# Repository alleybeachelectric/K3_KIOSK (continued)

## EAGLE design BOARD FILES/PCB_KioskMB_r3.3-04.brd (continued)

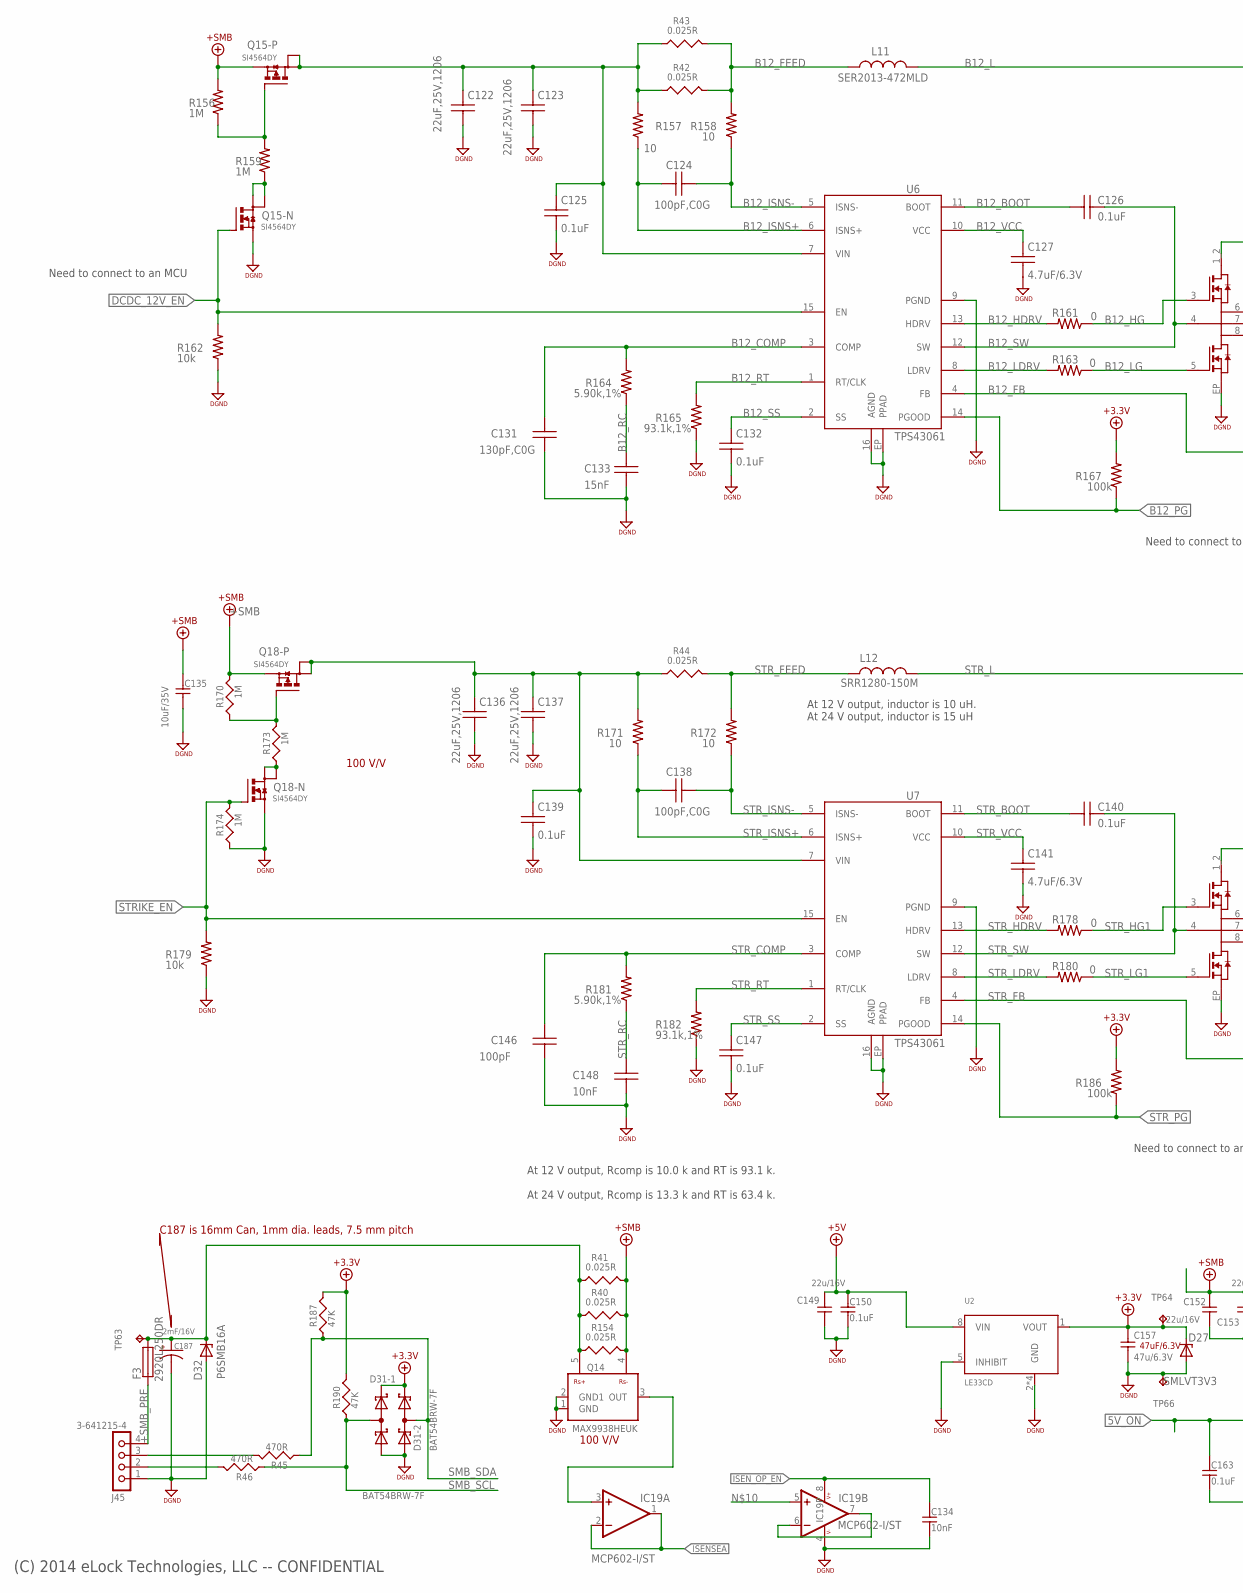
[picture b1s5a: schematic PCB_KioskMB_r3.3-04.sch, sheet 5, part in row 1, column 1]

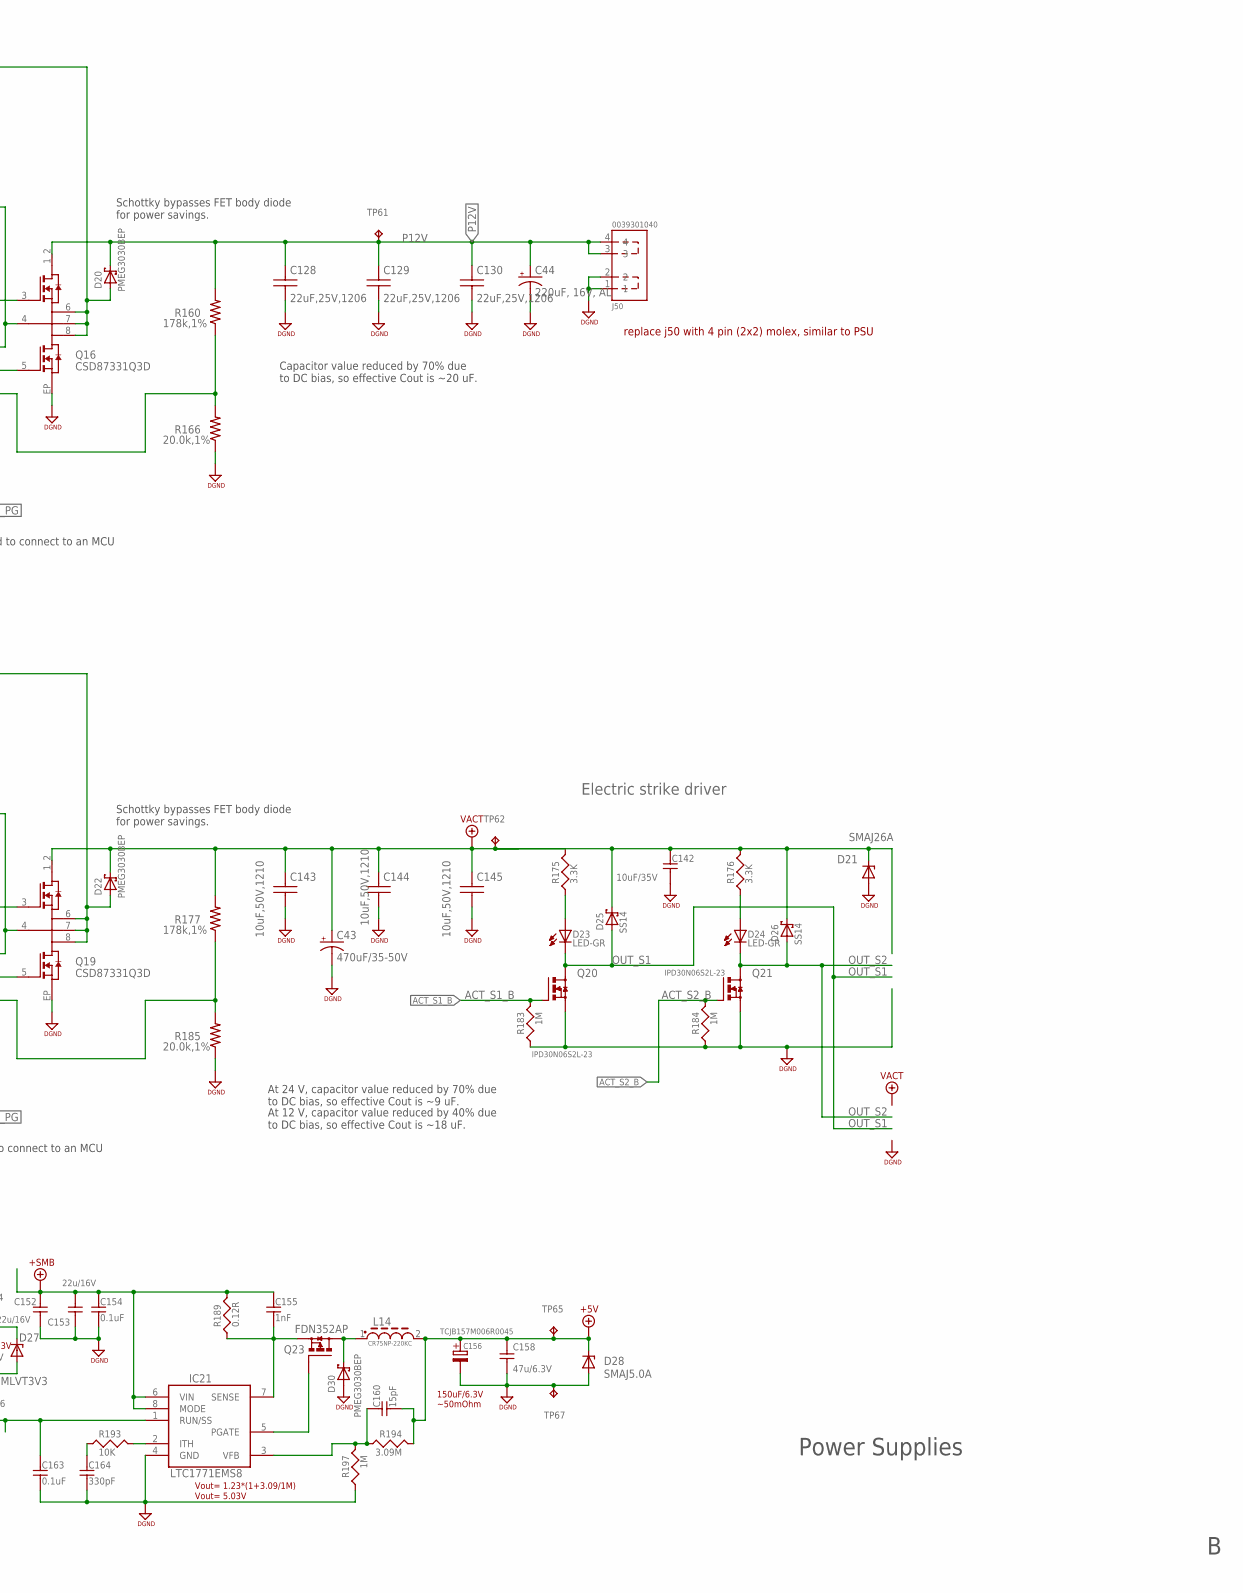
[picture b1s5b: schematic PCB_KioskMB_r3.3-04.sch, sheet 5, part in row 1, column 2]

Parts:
C43: 470uF/35-50V; E5-13
C44: 220uF, 16V, AL; 153CLV-0605
C122, C123, C128, C129, C130, C136, C137: 22uF,25V,1206; C1206; MFR_PN CL31A226KAHNNNE
C124, C138: 100pF,C0G; C0603; MFR_PN CL10C101JB8NCNC
C125, C126, C132, C139, C140, C147: 0.1uF; C0603; MFR_PN GRM188R71H104KA93D
C127, C141: 4.7uF/6.3V; C0603; MFR_PN CL10A475KA8NQNC
C131: 130pF,C0G; C0603; MFR_PN CL10C131JB8NNNC
C133: 15nF; C0603; MFR_PN CL10B153KB8NNNC
C134: 10nF; 0603
C135, C142: 10uF/35V; 1206
C143, C144, C145: 10uF,50V,1210; C1210; MFR_PN CL32B106KBJNNWE
C146: 100pF; C0603; MFR_PN CL10C101JB8NNNC
C148: 10nF; C0603; MFR_PN CL10B103KB8NNNC
C149, C152, C153: 22u/16V; 1210
C150, C154, C163: 0.1uF; 0603
C155: 1nF; 0603
C156: TCJB157M006R0045; 3528-POL
C157, C158: 47u/6.3V; 1210
C160: 15pF; 0603
C164: 330pF; 0603
C187: 2mF/16V; E7,5-18
D20, D22, D30: PMEG3030BEP; SOD-128
D21: SMAJ26A; SMA
D23, D24: LED-GR; 0805-POL
D25, D26: SS14; SMA
D27: SMLVT3V3; SMA
D28: SMAJ5.0A; SMA
D31: BAT54BRW-7F; SOT-363
D32: P6SMB16A; SMB
F3: 2920L250DR; 1812
IC19: MCP602-I/ST; TSSOP8
IC21: LTC1771EMS8; MSOP-08
J45: 3-641215-4
J50: 0039301040
L11: SER2013-472MLD; L_SER20XX; MFR_PN SER2013-472ML
L12: SRR1280-150M; L_SRR1280; MFR_PN SRR1280-1x0M
L14: CR75NP-220KC; CR75
Q14: MAX9938HEUK; SOT23-5
Q15, Q18: SI4564DY; SO-08
Q16, Q19: CSD87331Q3D; SON8_3.3X3.3_TI; MFR_PN CSD87331Q3D
Q20, Q21: IPD30N06S2L-23; TO252
Q23: FDN352AP; SOT-23
R40, R41, R42, R43, R44, R154: 0.025R; 0805
R45, R46: 470R; 0603
R156, R159: 1M; R0603; MFR_PN ERJ-3GEYJ104V
R157, R158, R171, R172: 10; R0603; MFR_PN MCR03ERTJ100
R160, R177: 178k,1%; R0603; MFR_PN ERJ-3EKF1783V
R161, R163, R178, R180: 0; R0603; MFR_PN ERJ-3GEY0R00V
R162, R179: 10k; R0603; MFR_PN ERJ-3GEYJ103V
R164: 5.90k,1%; R0603; MFR_PN ERJ-3EKF5901V
R165: 93.1k,1%; R0603; MFR_PN ERJ-3EKF9312V
R166, R185: 20.0k,1%; R0603; MFR_PN ERJ-3EKF2002V
R167, R186: 100k; R0603; MFR_PN ERJ-3GEYJ104V
R170, R173, R174, R183, R184, R197: 1M; 0603
R175, R176: 3.3K; 0805
R181: 5.90k,1%; R0603; MFR_PN ERJ-3EKFxxxxV
R182: 93.1k,1%; R0603; MFR_PN ERJ-3EKFxxxxV
R187, R190: 47K; 0603
R189: 0.12R; 0805
R193: 10K; 0603
R194: 3.09M; 0603
TP61, TP62, TP63, TP64, TP65, TP66, TP67: TPB1,27; B1,27
U2: LE33CD; LE33
U6, U7: TPS43061; QFN16_3X3_EP

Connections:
5V_ON: C163.1, IC21.1 (RUN/SS); also elsewhere on the board
+3.3V: C157.1, D27.+ (C), D31.4 (K), D31.5 (K), R167.2, R186.2, R187.2, R190.2, TP64.TP, U2.1 (VOUT); also elsewhere on the board
+5V: C149.1, C150.1, C156.1 (PIN+), C158.1, C160.2, D28.+ (C), L14.2, R194.1, TP65.TP, U2.8 (VIN); also elsewhere on the board
+SMB: C135.1, C152.1, C153.1, C154.1, C155.1, IC21.6 (VIN), IC21.8 (MODE), Q14.4 (VIN-), Q15.3 (S), Q18.3 (S), R40.2, R41.2, R154.2, R156.2, R170.1, R189.2; also elsewhere on the board
+SMB_PRE: F3.1, J45.4; also elsewhere on the board
ACT_S1_B: Q20.1 (G), R183.1; also elsewhere on the board
ACT_S2_B: Q21.1 (G), R184.1; also elsewhere on the board
B12_BOOT: C126.1, U6.11 (BOOT)
B12_COMP: C131.1, R164.2, U6.3 (COMP)
B12_FB: R160.1, R166.2, U6.4 (FB)
B12_FEED: L11.2, R42.2, R43.2, R158.2
B12_HDRV: R161.2, U6.13 (HDRV)
B12_HG: Q16.3 (TG), R161.1
B12_ISNS+: C124.1, R157.1, U6.6 (ISNS+)
B12_ISNS-: C124.2, R158.1, U6.5 (ISNS-)
B12_L: D20.A, L11.1, Q16.6 (VSW), Q16.7 (VSW), Q16.8 (VSW)
B12_LDRV: R163.2, U6.8 (LDRV)
B12_LG: Q16.5 (BG), R163.1
B12_PG: R167.1, U6.14 (PGOOD); also elsewhere on the board
B12_RC: C133.1, R164.1
B12_RT: R165.2, U6.1 (RT/CLK)
B12_SS: C132.1, U6.2 (SS)
B12_SW: C126.2, Q16.4 (TGR), U6.12 (SW)
B12_VCC: C127.1, U6.10 (VCC)
DCDC12VIN: C122.1, C123.1, C125.1, Q15.5 (D), Q15.6 (D1), R42.1, R43.1, R157.2, U6.7 (VIN)
DCDC_12V_EN: Q15.2 (G), R162.2, U6.15 (EN); also elsewhere on the board
DGND: C43.-, C44.-, C122.2, C123.2, C125.2, C127.2, C128.2, C129.2, C130.2, C131.2, C132.2, C133.2, C134.2, C135.2, C136.2, C137.2, C139.2, C141.2, C142.2, C143.2, C144.2, C145.2, C146.2, C147.2, C148.2, C149.2, C150.2, C152.2, C153.2, C154.2, C156.2 (PIN-), C157.2, C158.2, C163.2, C164.2, C187.-, D21.- (A), D27.- (A), D28.- (A), D30.A, D31.1 (A), D31.2 (A), D32.A, IC19.4 (V-), IC21.4 (GND), J45.1, J50.1, J50.2, Q14.1 (GND), Q14.2 (GND1), Q15.1 (S), Q16.EP (PGND), Q18.1 (S), Q19.EP (PGND), Q20.2 (S), Q21.2 (S), R162.1, R165.1, R166.1, R174.2, R179.1, R182.1, R183.2, R184.2, R185.1, R197.2, TP66.TP, TP67.TP, U2.2 (GND), U2.3 (GND), U2.5 (INHIBIT), U2.6 (GND), U2.7 (GND), U6.9 (PGND), U6.16 (AGND), U6.EP (PPAD), U7.9 (PGND), U7.16 (AGND), U7.EP (PPAD); also elsewhere on the board
ISENSEA: IC19.1 (OUT), IC19.2 (-IN); also elsewhere on the board
ISEN_OP_EN: C134.1, IC19.8 (V+); also elsewhere on the board
unnamed: IC19.6 (-IN), IC19.7 (OUT)
unnamed: IC21.5 (PGATE), Q23.1 (G)
unnamed: C187.+, D32.C, F3.2, Q14.5 (VIN+), R40.1, R41.1, R154.1, TP63.TP
unnamed: IC19.3 (+IN), IC19.5 (+IN), Q14.3 (OUT)
unnamed: IC21.2 (ITH), R193.2
unnamed: C164.1, R193.1
unnamed: D30.K, L14.1, Q23.3 (D)
unnamed: C155.2, IC21.7 (SENSE), Q23.2 (S), R189.1
unnamed: Q15.4 (G), R156.1, R159.2
unnamed: C160.1, IC21.3 (VFB), R194.2, R197.1
unnamed: J45.2, R46.2
unnamed: D23.2 (A), R175.1
unnamed: D24.2 (A), R176.1
unnamed: J45.3, R45.2
unnamed: Q18.4 (G), R170.2, R173.1
unnamed: Q15.7 (D), Q15.8 (D1), R159.1
unnamed: Q18.7 (D), Q18.8 (D1), R173.2
OUT_S1: D23.1+ (K), D25.A, Q20.3 (D); also elsewhere on the board
OUT_S2: D24.1+ (K), D26.A, Q21.3 (D); also elsewhere on the board
P12V: C44.+, C128.1, C129.1, C130.1, D20.K, J50.3, J50.4, Q16.1_2 (VIN), R160.2, TP61.TP; also elsewhere on the board
SMB_SCL: D31.6 (AK), R46.1, R190.1; also elsewhere on the board
SMB_SDA: D31.3 (AK), R45.1, R187.1; also elsewhere on the board
STRIKE_EN: Q18.2 (G), R174.1, R179.2, U7.15 (EN); also elsewhere on the board
STR_BOOT: C140.1, U7.11 (BOOT)
STR_COMP: C146.1, R181.2, U7.3 (COMP)
STR_FB: R177.1, R185.2, U7.4 (FB)
STR_FEED: L12.2, R44.2, R172.2
STR_HDRV: R178.2, U7.13 (HDRV)
STR_HG1: Q19.3 (TG), R178.1
STR_ISNS+: C138.1, R171.1, U7.6 (ISNS+)
STR_ISNS-: C138.2, R172.1, U7.5 (ISNS-)
STR_L: D22.A, L12.1, Q19.6 (VSW), Q19.7 (VSW), Q19.8 (VSW)
STR_LDRV: R180.2, U7.8 (LDRV)
STR_LG1: Q19.5 (BG), R180.1
STR_PG: R186.1, U7.14 (PGOOD); also elsewhere on the board
STR_RC: C148.1, R181.1
STR_RT: R182.2, U7.1 (RT/CLK)
STR_SS: C147.1, U7.2 (SS)
STR_SW: C140.2, Q19.4 (TGR), U7.12 (SW)
STR_VCC: C141.1, U7.10 (VCC)
VACT: C43.+, C142.1, C143.1, C144.1, C145.1, D21.+ (C), D22.K, D25.C (K), D26.C (K), Q19.1_2 (VIN), R175.2, R176.2, R177.2, TP62.TP; also elsewhere on the board
VSUPLYACT: C136.1, C137.1, C139.1, Q18.5 (D), Q18.6 (D1), R44.1, R171.2, U7.7 (VIN)

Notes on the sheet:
(C) 2014 eLock Technologies, LLC -- CONFIDENTIAL
Power Supplies
Schottky bypasses FET body diode for power savings.
Capacitor value reduced by 70% due to DC bias, so effective Cout is ~20 uF.
At 24 V, capacitor value reduced by 70% due to DC bias, so effective Cout is ~9 uF.
At 12 V, capacitor value reduced by 40% due to DC bias, so effective Cout is ~18 uF.
At 12 V output, inductor is 10 uH. At 24 V output, inductor is 15 uH
At 12 V output, Rcomp is 10.0 k and RT is 93.1 k. At 24 V output, Rcomp is 13.3 k and RT is 63.4 k.
47uF/6.3V
Electric strike driver
100 V/V
Vout= 1.23*(1+3.09/1M)
Vout= 5.03V
150uF/6.3V ~50mOhm
Need to connect to an MCU
C187 is 16mm Can, 1mm dia. leads, 7.5 mm pitch
replace j50 with 4 pin (2x2) molex, similar to PSU

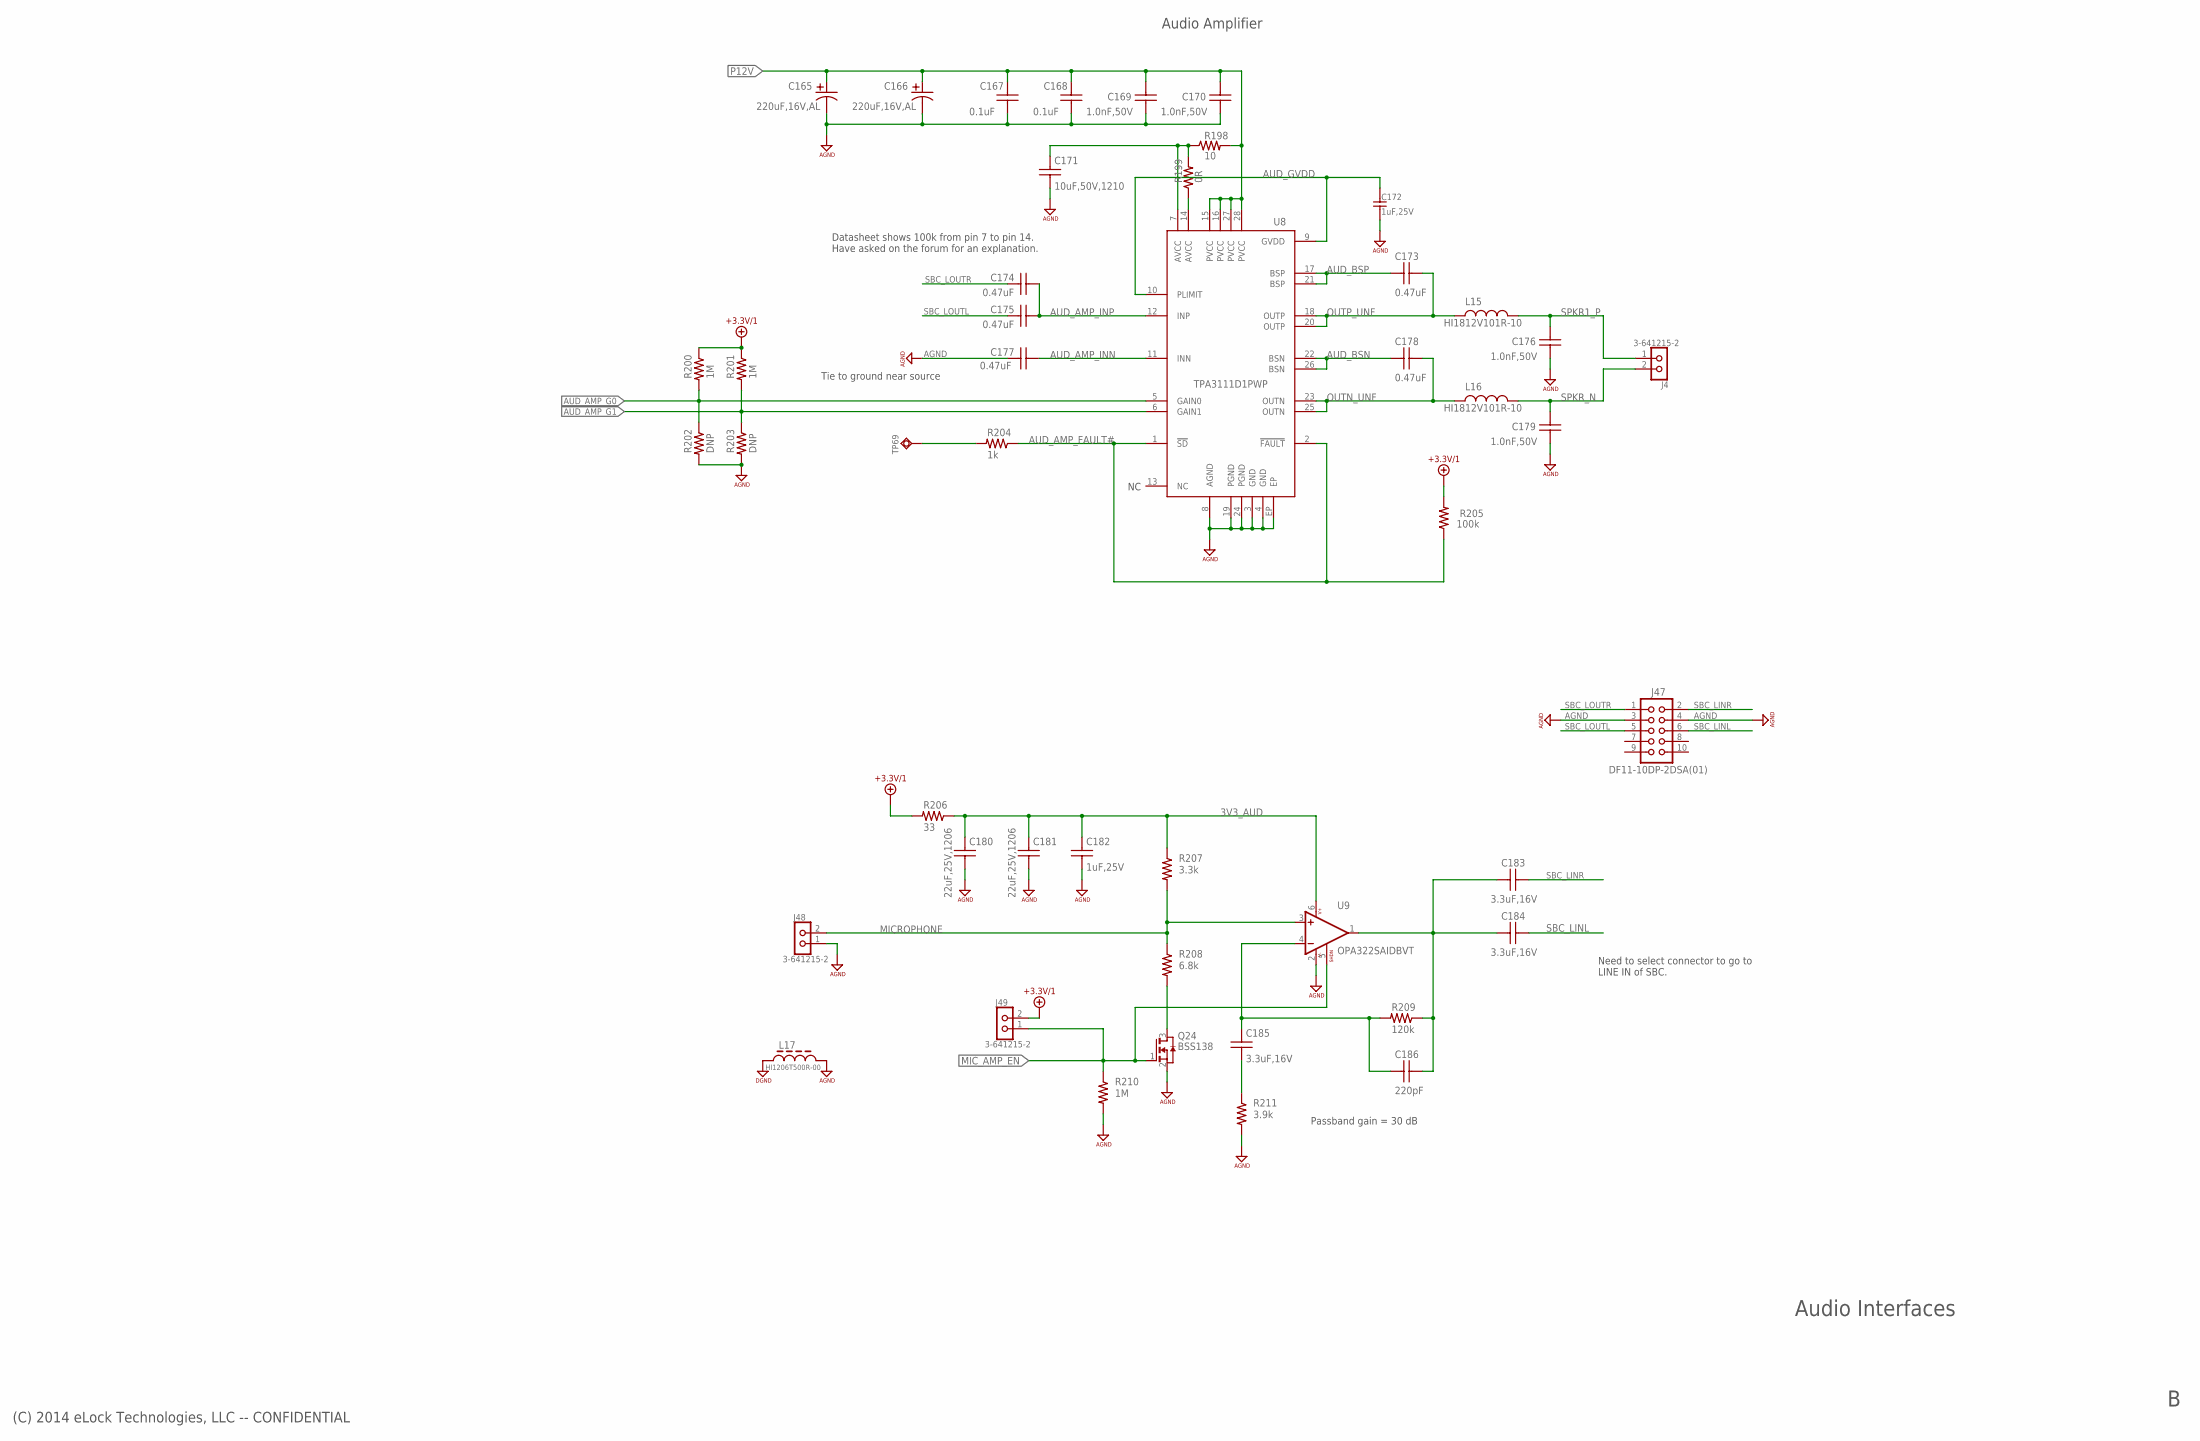
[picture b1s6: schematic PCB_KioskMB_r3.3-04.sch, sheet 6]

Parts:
C165, C166: 220uF,16V,AL; CAP_6.3MM_DIA_SMT; MFR_PN EEV227M016A9HAA
C167, C168: 0.1uF; C0603
C169, C170, C176, C179: 1.0nF,50V; C0603; MFR_PN CL10B102KB8NNNC
C171: 10uF,50V,1210; C1210; MFR_PN CL32B106KBJNNWE
C172: 1uF,25V; 0603
C173, C178: 0.47uF; C0603; MFR_PN TMK107B7474KA-TR
C174, C175, C177: 0.47uF; C0603; MFR_PN CL10B153KB8NNNC
C180, C181: 22uF,25V,1206; C1206; MFR_PN CL31A226KAHNNNE
C182: 1uF,25V; C0603
C183, C184, C185: 3.3uF,16V; C0603
C186: 220pF; C0603
J4, J48, J49: 3-641215-2
J47: DF11-10DP-2DSA(01); DF11-10DP-2DSA
L15, L16: HI1812V101R-10; L1812; MFR_PN HI1812V101R-10
L17: HI1206T500R-00; 1206
Q24: BSS138; SOT23
R198: 10; R0603; MFR_PN MCR03ERTJ100
R199: 0R; R0603; MFR_PN MCR03ERTJ100
R200, R201, R210: 1M; R0603
R202, R203: DNP; R0603
R204: 1k; R0603
R205: 100k; R0603
R206: 33; R0603
R207: 3.3k; R0603
R208: 6.8k; R0603
R209: 120k; R0603
R211: 3.9k; R0603
TP69: P1-13; P1-13@1
U8: TPA3111D1PWP; TSSOP28_EP
U9: OPA322SAIDBVT; SOT23-6

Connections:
3V3_AUD: C180.1, C181.1, C182.1, R206.1, R207.1, U9.6 (V+)
+3.3V/1: J49.2, R200.1, R201.1, R205.2, R206.2; also elsewhere on the board
AGND: C165.2, C166.2, C167.2, C168.2, C169.2, C170.2, C171.2, C172.2, C176.2, C177.1, C179.2, C180.2, C181.2, C182.2, J47.3, J47.4, J48.1, L17.2, Q24.2 (S), R202.2, R203.2, R210.2, R211.2, U8.3 (GND), U8.4 (GND), U8.8 (AGND), U8.19 (PGND), U8.24 (PGND), U8.EP, U9.2 (V-); also elsewhere on the board
AUD_AMP_FAULT#: R204.1, R205.1, U8.1 (!SD), U8.2 (!FAULT)
AUD_AMP_G0: R200.2, R202.1, U8.5 (GAIN0); also elsewhere on the board
AUD_AMP_G1: R201.2, R203.1, U8.6 (GAIN1); also elsewhere on the board
AUD_AMP_INN: C177.2, U8.11 (INN)
AUD_AMP_INP: C174.2, C175.2, U8.12 (INP)
AUD_AMP_SD#: R204.2, TP69.1
AUD_BSN: C178.1, U8.22 (BSN), U8.26 (BSN)
AUD_BSP: C173.1, U8.17 (BSP), U8.21 (BSP)
AUD_GVDD: C172.1, U8.9 (GVDD), U8.10 (PLIMIT)
DGND: L17.1; also elsewhere on the board
MICROPHONE: J48.2, R207.2, R208.1, U9.3 (+IN); also elsewhere on the board
MIC_AMP_EN: J49.1, Q24.1 (G), R210.1, U9.5 (!SHDN); also elsewhere on the board
unnamed: R199.1, U8.14 (AVCC)
unnamed: C171.1, R198.1, R199.2, U8.7 (AVCC)
unnamed: C185.2, R211.1
unnamed: C185.1, C186.1, R209.2, U9.4 (-IN)
unnamed: C183.1, C184.1, C186.2, R209.1, U9.1 (OUT)
unnamed: Q24.3 (D), R208.2
OUTN_UNF: C178.2, L16.2, U8.23 (OUTN), U8.25 (OUTN)
OUTP_UNF: C173.2, L15.2, U8.18 (OUTP), U8.20 (OUTP)
P12V: C165.1, C166.1, C167.1, C168.1, C169.1, C170.1, R198.2, U8.15 (PVCC), U8.16 (PVCC), U8.27 (PVCC), U8.28 (PVCC); also elsewhere on the board
SBC_LINL: C184.2, J47.6; also elsewhere on the board
SBC_LINR: C183.2, J47.2; also elsewhere on the board
SBC_LOUTL: C175.1, J47.5; also elsewhere on the board
SBC_LOUTR: C174.1, J47.1; also elsewhere on the board
SPKR1_P: C176.1, J4.1, L15.1; also elsewhere on the board
SPKR_N: C179.1, J4.2, L16.1; also elsewhere on the board

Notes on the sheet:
(C) 2014 eLock Technologies, LLC -- CONFIDENTIAL
Audio Interfaces
Tie to ground near source
Datasheet shows 100k from pin 7 to pin 14. Have asked on the forum for an explanation.
Audio Amplifier
Passband gain = 30 dB
Need to select connector to go to LINE IN of SBC.

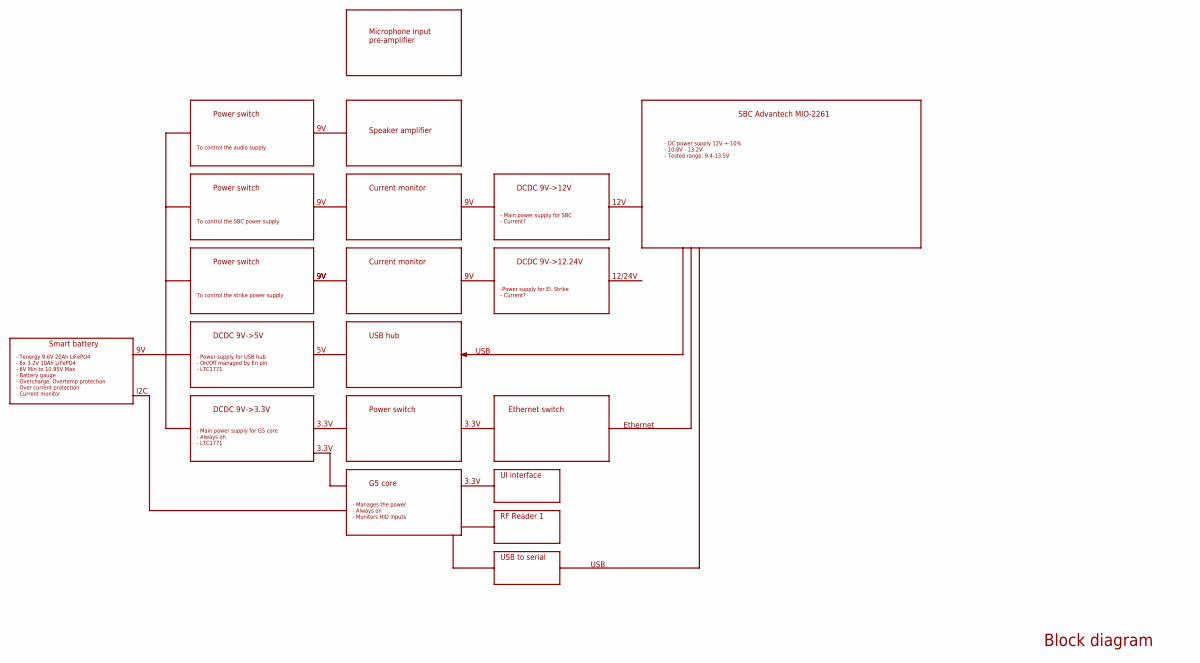
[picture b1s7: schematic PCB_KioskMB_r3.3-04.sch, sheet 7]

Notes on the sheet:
Block diagram
SBC Advantech MIO-2261
Microphone input pre-amplifier
Speaker amplifier
Smart battery
- Tenergy 9.6V 20Ah LiFePO4 - 6x 3.2V 10Ah LiFePO4 - 6V Min to 10.95V Max - Battery gauge - Overcharge, Overtemp protection - Over current protection - Current monitor
I2C
DCDC 9V->12V
- Main power supply for SBC - Current?
- DC power supply 12V +-10% - 10.8V - 13.2V - Tested range: 9.4-13.5V
Power switch
To control the SBC power supply
12V
DCDC 9V->5V
- Power supply for USB hub - On/Off managed by En pin - LTC1771
DCDC 9V->12.24V
-Power supply for El. Strike - Current?
12/24V
To control the strike power supply
Current monitor
DCDC 9V->3.3V
- Main power supply for G5 core - Always on - LTC1771
3.3V
G5 core
- Manages the power - Always on - Monitors HID inputs
UI interface
RF Reader 1
USB hub
To control the audio supply
Ethernet switch
USB
Ethernet
USB to serial

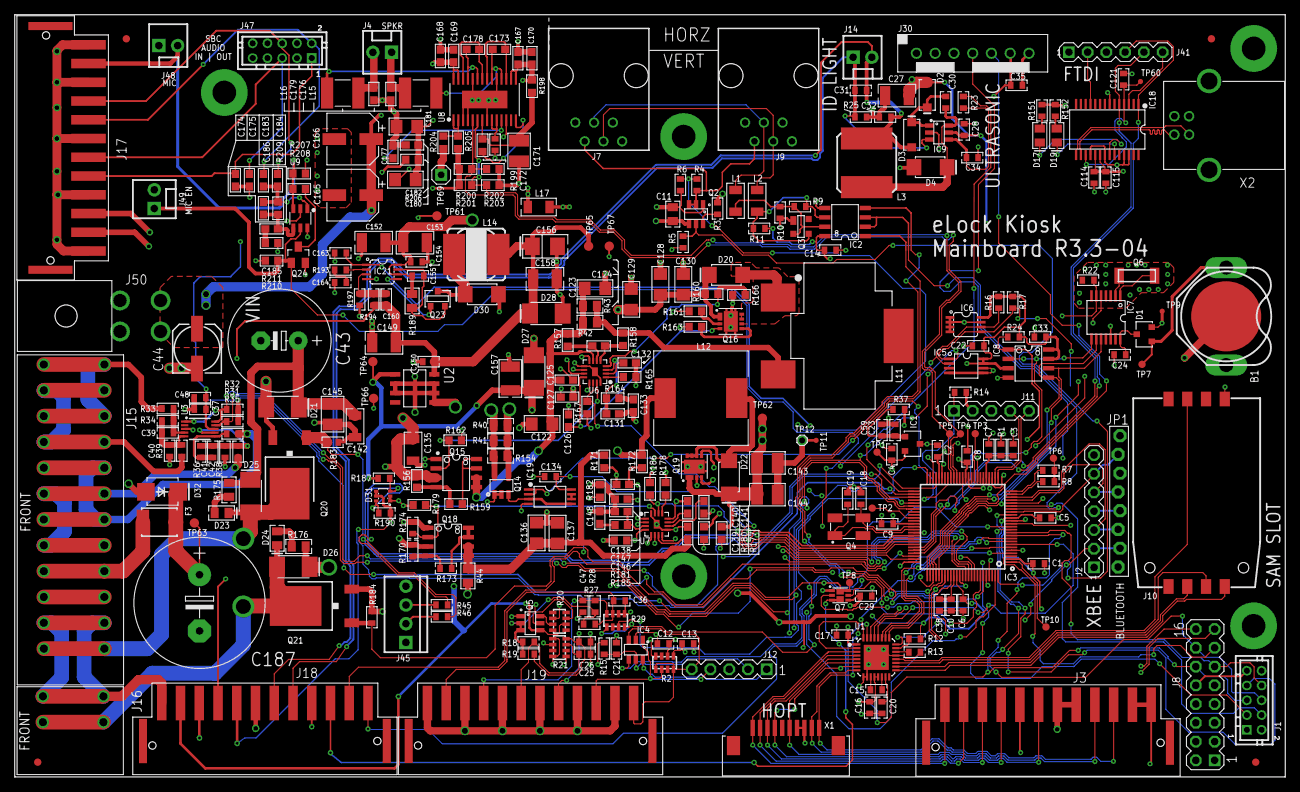
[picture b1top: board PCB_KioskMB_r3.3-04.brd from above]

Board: 4 copper layers, 172.1 x 103.3 mm, 328 parts (0 on the bottom side), 222 nets.

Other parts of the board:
DRILEGEND: DRILEGEND

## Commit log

2017-05-10 initial commit.
2017-05-15 getting closer.
2017-05-18 almost there again. fixed FPC connector to be 1.00mm pitch.
2017-05-18 save state 12:27pm
    save state 12:27pm
2017-05-23 update from thursday
    update from thursday
2017-05-25 finished routing. todo : finish DRC errors.
2017-05-29 added BOM to csv
2017-05-29 cleaned up silk
2017-05-30 updated BOM
2017-06-30 added components ( for sbc power) and updated lan components.
2017-06-30 ADDED SILK
2017-07-04 update connectors
    USB B connector, VREF design, connectors.
2017-07-04 added molex connector
2017-07-04 push latest
2017-07-06 new rev number
    major changes, reviewed all of Jarv's notes and applied them. started changing connectors.
2017-07-07 DAMN
    A lot of work done, finished Jarv's notes, added BT, and a few more things
2017-07-07 :+1:
    :P
2017-07-07 added .png of connectors.
2017-07-10 finished routing. cleaned up top silk
2017-07-10 added bottom silk
2017-07-11 finalized bottom silk
    finalized bottom silk, added 8 different revisions of bottom silk. added icons to match solar charger controller
2017-07-11 added fab file release folder and gerbers
2017-07-12 on r3.3-05
2017-08-18 added 3.4
2018-03-08 cleaned up repo
